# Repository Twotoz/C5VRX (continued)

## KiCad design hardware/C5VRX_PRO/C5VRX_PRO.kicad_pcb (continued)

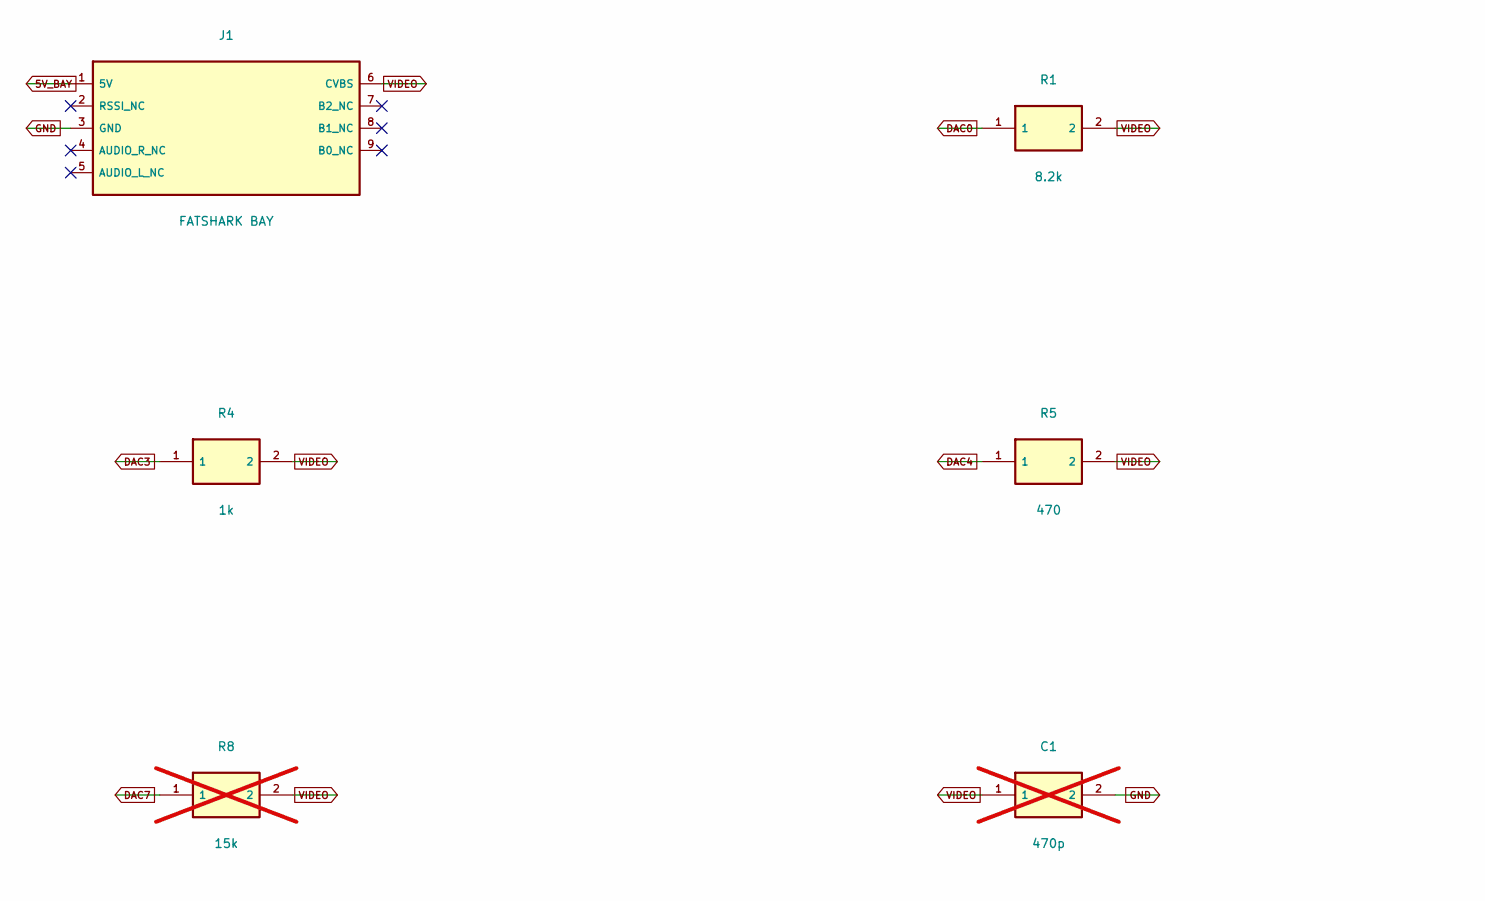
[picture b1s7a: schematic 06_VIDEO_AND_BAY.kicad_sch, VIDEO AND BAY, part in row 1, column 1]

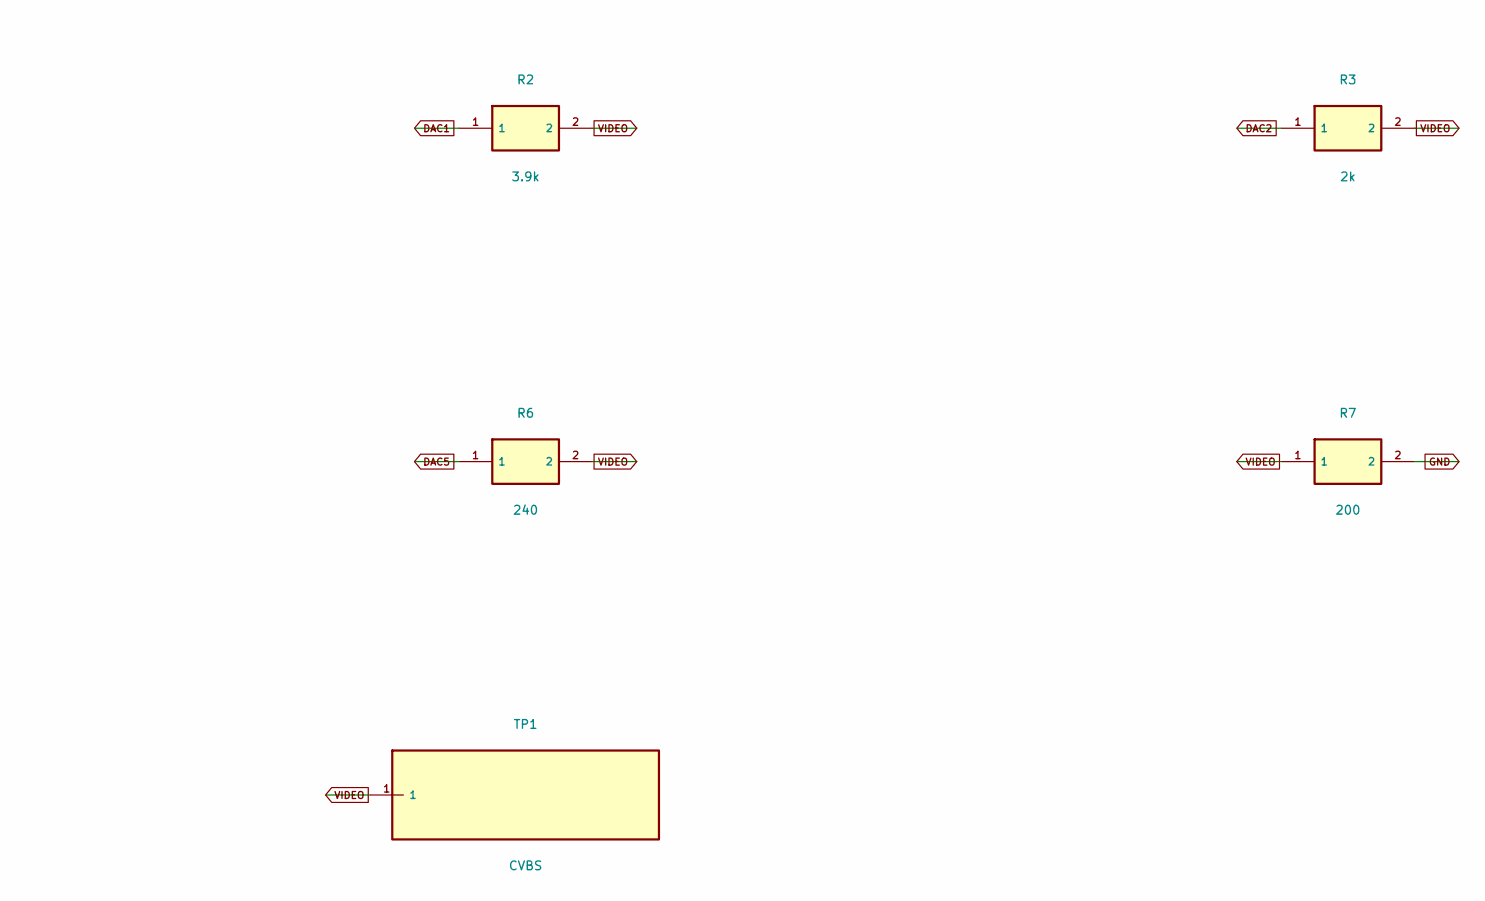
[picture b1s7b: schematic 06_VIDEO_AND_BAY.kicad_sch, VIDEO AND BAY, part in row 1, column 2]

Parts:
C1: 470p; Capacitor_SMD__C_0402_1005Metric; MPN GRM1555C1H471JA01D; not fitted
J1: FATSHARK BAY; FatShark_Header_1x09; MPN CUSTOM_1x09_P2.54_BAY
R1: 8.2k; Resistor_SMD__R_0402_1005Metric; MPN RT0402BRD078K2L
R2: 3.9k; Resistor_SMD__R_0402_1005Metric; MPN RT0402BRD073K9L
R3: 2k; Resistor_SMD__R_0402_1005Metric; MPN RT0402BRD072KL
R4: 1k; Resistor_SMD__R_0402_1005Metric; MPN RT0402BRD071KL
R5: 470; Resistor_SMD__R_0402_1005Metric; MPN RT0402BRD07470RL
R6: 240; Resistor_SMD__R_0402_1005Metric; MPN RT0402BRD07240RL
R7: 200; Resistor_SMD__R_0402_1005Metric; MPN RT0402BRD07200RL
R8: 15k; Resistor_SMD__R_0402_1005Metric; MPN RT0402BRD0715KL; not fitted
TP1: CVBS; TestPoint__TestPoint_Pad_D1.5mm; MPN PCB_FEATURE

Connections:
5V_BAY: J1.1 (5V); also elsewhere on the board
DAC0: R1.1; also elsewhere on the board
DAC1: R2.1; also elsewhere on the board
DAC2: R3.1; also elsewhere on the board
DAC3: R4.1; also elsewhere on the board
DAC4: R5.1; also elsewhere on the board
DAC5: R6.1; also elsewhere on the board
DAC7: R8.1; also elsewhere on the board
GND: C1.2, J1.3 (GND), R7.2; also elsewhere on the board
VIDEO: C1.1, J1.6 (CVBS), R1.2, R2.2, R3.2, R4.2, R5.2, R6.2, R7.1, R8.2, TP1.1

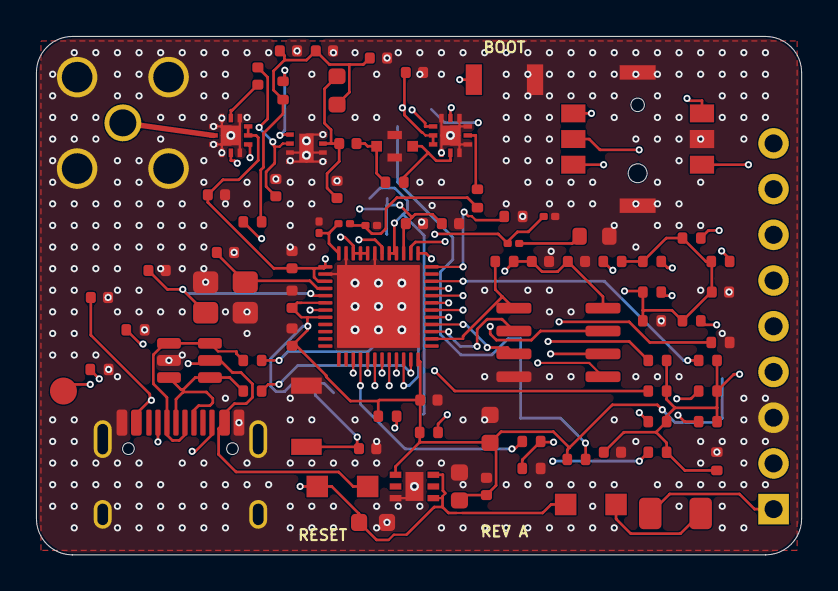
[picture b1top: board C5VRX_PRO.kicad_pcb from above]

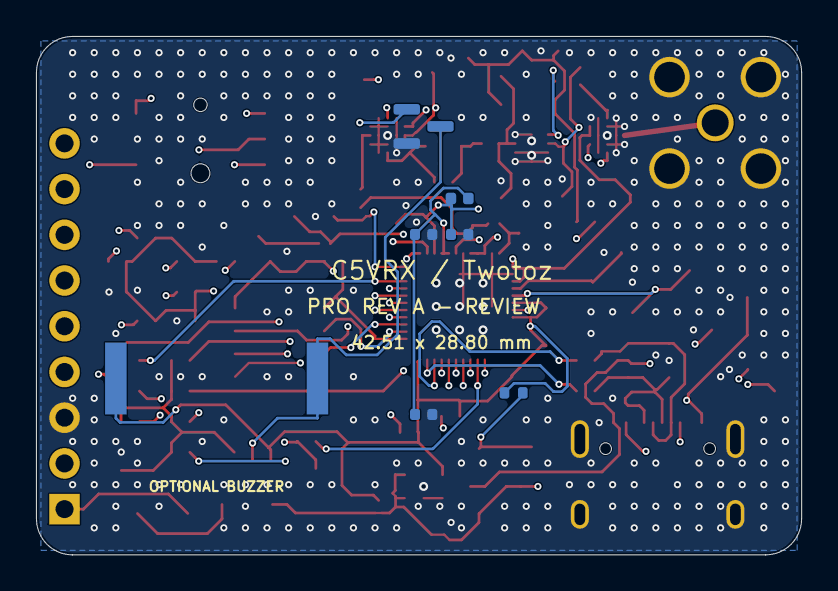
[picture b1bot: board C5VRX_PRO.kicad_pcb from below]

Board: 4 copper layers, 42.5 x 28.8 mm, 91 parts (7 on the bottom side), 57 nets.

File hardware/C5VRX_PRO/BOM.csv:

Reference,Value,Manufacturer,MPN,Footprint,Populate,Note,Datasheet
U1,ESP32-C5HR2,Espressif,ESP32-C5HR2,PRO:Package_DFN_QFN__QFN-48-1EP_6x6mm_P0.4mm_EP4.6x4.6mm,YES,,https://www.espressif.com/sites/default/files/documentation/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
U2,W25Q64JVSSIQ,Winbond,W25Q64JVSSIQ,PRO:Package_SO__SOIC-8_3.9x4.9mm_P1.27mm,YES,,
R10,10k,Yageo,RC0402FR-0710KL,PRO:Resistor_SMD__R_0402_1005Metric,YES,1%; ,
C10,100n,Murata,GRM155R71C104KA88D,PRO:Capacitor_SMD__C_0402_1005Metric,YES,,
C11,1u,Murata,GRM155R61A105KE15D,PRO:Capacitor_SMD__C_0402_1005Metric,YES,,
Y1,48MHz / CL18pF,Abracon,ABM8-48.000MHZ-B2-T,PRO:Crystal__Crystal_SMD_3225-4Pin_3.2x2.5mm,YES,,
C12,27p,Murata,GRM1555C1H270JA01D,PRO:Capacitor_SMD__C_0402_1005Metric,YES,Initial CL value; tune with measured stray capacitance,
C13,27p,Murata,GRM1555C1H270JA01D,PRO:Capacitor_SMD__C_0402_1005Metric,YES,,
R11,10k,Yageo,RC0402FR-0710KL,PRO:Resistor_SMD__R_0402_1005Metric,YES,1%; ,
C14,1u,Murata,GRM155R61A105KE15D,PRO:Capacitor_SMD__C_0402_1005Metric,YES,,
R12,10k,Yageo,RC0402FR-0710KL,PRO:Resistor_SMD__R_0402_1005Metric,YES,1%; ,
R13,10k,Yageo,RC0402FR-0710KL,PRO:Resistor_SMD__R_0402_1005Metric,YES,1%; GPIO27 high for USB download boot; keep loopback loading small,
R14,100k,Yageo,RC0402FR-07100KL,PRO:Resistor_SMD__R_0402_1005Metric,YES,"1%; GPIO7 JTAG strap, no LED loading",
R15,100k,Yageo,RC0402FR-07100KL,PRO:Resistor_SMD__R_0402_1005Metric,YES,1%; Fail to passive bypass during reset,
C20,100n,Murata,GRM155R71C104KA88D,PRO:Capacitor_SMD__C_0402_1005Metric,YES,,
C21,100n,Murata,GRM155R71C104KA88D,PRO:Capacitor_SMD__C_0402_1005Metric,YES,,
C22,100n,Murata,GRM155R71C104KA88D,PRO:Capacitor_SMD__C_0402_1005Metric,YES,,
C23,100n,Murata,GRM155R71C104KA88D,PRO:Capacitor_SMD__C_0402_1005Metric,YES,,
C24,100n,Murata,GRM155R71C104KA88D,PRO:Capacitor_SMD__C_0402_1005Metric,YES,,
C25,100n,Murata,GRM155R71C104KA88D,PRO:Capacitor_SMD__C_0402_1005Metric,YES,,
C26,100n,Murata,GRM155R71C104KA88D,PRO:Capacitor_SMD__C_0402_1005Metric,YES,,
C27,10u,Murata,GRM188R61A106KE69D,PRO:Capacitor_SMD__C_0603_1608Metric,YES,,
L2,2nH,Murata,LQG15HS2N0S02D,PRO:Inductor_SMD__L_0402_1005Metric,YES,ESP RF supply initial tuning value,
C28,1u,Murata,GRM155R61A105KE15D,PRO:Capacitor_SMD__C_0402_1005Metric,YES,,
C29,100n,Murata,GRM155R71C104KA88D,PRO:Capacitor_SMD__C_0402_1005Metric,YES,,
J1,FATSHARK BAY,PCBWay sourcing,CUSTOM_1x09_P2.54_BAY,PRO:FatShark_Header_1x09,YES,,
J3,SMA 50R,Amphenol RF,132134,PRO:Connector_Coaxial__SMA_Amphenol_132134_Vertical,YES,"Vertical SMA female, through-hole, antenna normal to PCB",
J4,USB-C,HRO,TYPE-C-31-M-12,PRO:Connector_USB__USB_C_Receptacle_HRO_TYPE-C-31-M-12,YES,,
R20,5.1k,Yageo,RC0402FR-075K1L,PRO:Resistor_SMD__R_0402_1005Metric,YES,1%; ,
R21,5.1k,Yageo,RC0402FR-075K1L,PRO:Resistor_SMD__R_0402_1005Metric,YES,1%; ,
R22,22,Yageo,RC0402FR-0722RL,PRO:Resistor_SMD__R_0402_1005Metric,YES,1%; ,
R23,22,Yageo,RC0402FR-0722RL,PRO:Resistor_SMD__R_0402_1005Metric,YES,1%; ,
U6,USBLC6-2SC6,STMicroelectronics,USBLC6-2SC6,PRO:Package_TO_SOT_SMD__SOT-23-6,YES,,
F1,750mA PTC,Littelfuse,1206L075/13.2WR,PRO:Fuse__Fuse_1206_3216Metric,YES,,
D1,PMEG2010ER,Nexperia,"PMEG2010ER,115",PRO:Diode_SMD__Nexperia_CFP3_SOD-123W,YES,,
D2,PMEG2010ER,Nexperia,"PMEG2010ER,115",PRO:Diode_SMD__Nexperia_CFP3_SOD-123W,YES,,
U7,TLV75733PDRVR,Texas Instruments,TLV75733PDRVR,PRO:Package_DFN_QFN__DFN-6-1EP_2x2mm_P0.65mm_EP1x1.6mm,YES,,
C30,10u,Murata,GRM188R61A106KE69D,PRO:Capacitor_SMD__C_0603_1608Metric,YES,,
C31,10u,Murata,GRM188R61A106KE69D,PRO:Capacitor_SMD__C_0603_1608Metric,YES,,
C32,100n,Murata,GRM155R71C104KA88D,PRO:Capacitor_SMD__C_0402_1005Metric,YES,,
C33,1u,Murata,GRM155R61A105KE15D,PRO:Capacitor_SMD__C_0402_1005Metric,YES,,
SW1,BOOT,Omron,B3U-1000P,PRO:Button_Switch_SMD__SW_SPST_B3U-1000P,YES,,
SW2,RESET,Omron,B3U-1000P,PRO:Button_Switch_SMD__SW_SPST_B3U-1000P,YES,,
SW3,5-WAY JOYSTICK,ALPS Alpine,SKRHABE010,PRO:SW_SKRHABE010_SMD,YES,,
R30,10k,Yageo,RC0402FR-0710KL,PRO:Resistor_SMD__R_0402_1005Metric,YES,1%; ,
R31,22k,Yageo,RC0402FR-0722KL,PRO:Resistor_SMD__R_0402_1005Metric,YES,1%; ,
R32,1k,Yageo,RC0402FR-071KL,PRO:Resistor_SMD__R_0402_1005Metric,YES,1%; ,
R33,2.2k,Yageo,RC0402FR-072K2L,PRO:Resistor_SMD__R_0402_1005Metric,YES,1%; ,
R34,4.7k,Yageo,RC0402FR-074K7L,PRO:Resistor_SMD__R_0402_1005Metric,YES,1%; ,
R35,10k,Yageo,RC0402FR-0710KL,PRO:Resistor_SMD__R_0402_1005Metric,YES,1%; ,
R36,22,Yageo,RC0402FR-0722RL,PRO:Resistor_SMD__R_0402_1005Metric,YES,1%; ,
C34,100n,Murata,GRM155R71C104KA88D,PRO:Capacitor_SMD__C_0402_1005Metric,YES,,
R1,8.2k,Yageo,RT0402BRD078K2L,PRO:Resistor_SMD__R_0402_1005Metric,YES,0.1% thin film; ,
R2,3.9k,Yageo,RT0402BRD073K9L,PRO:Resistor_SMD__R_0402_1005Metric,YES,0.1% thin film; ,
R3,2k,Yageo,RT0402BRD072KL,PRO:Resistor_SMD__R_0402_1005Metric,YES,0.1% thin film; ,
R4,1k,Yageo,RT0402BRD071KL,PRO:Resistor_SMD__R_0402_1005Metric,YES,0.1% thin film; ,
R5,470,Yageo,RT0402BRD07470RL,PRO:Resistor_SMD__R_0402_1005Metric,YES,0.1% thin film; ,
R6,240,Yageo,RT0402BRD07240RL,PRO:Resistor_SMD__R_0402_1005Metric,YES,0.1% thin film; ,
R7,200,Yageo,RT0402BRD07200RL,PRO:Resistor_SMD__R_0402_1005Metric,YES,0.1% thin film; ,
R8,15k,Yageo,RT0402BRD0715KL,PRO:Resistor_SMD__R_0402_1005Metric,DNP,0.1% thin film; Future new LSB; current firmware is six bit,
C1,470p,Murata,GRM1555C1H471JA01D,PRO:Capacitor_SMD__C_0402_1005Metric,DNP,"Optional, verify video bandwidth before fitting",
BZ1,PASSIVE PIEZO,Murata,PKLCS1212E4001-R1,PRO:Buzzer_Beeper__Buzzer_Murata_PKLCS1212E,DNP,Optional reverse side SMD part; verify bay depth,
Q1,2N7002,Nexperia,"2N7002,215",PRO:Package_TO_SOT_SMD__SOT-23,DNP,,
R37,100,Yageo,RC0402FR-07100RL,PRO:Resistor_SMD__R_0402_1005Metric,DNP,1%; ,
R38,100k,Yageo,RC0402FR-07100KL,PRO:Resistor_SMD__R_0402_1005Metric,DNP,1%; ,
U3,PE42422,pSemi,PE42422A-X,PRO:PE42422_QFN12,YES,,
U5,PE42422,pSemi,PE42422A-X,PRO:PE42422_QFN12,YES,,
U4,QPL9504,Qorvo,QPL9504TR7,PRO:QPL9504_DFN8,YES,,
C40,5.6p,Murata,GJM1555C1H5R6CB01D,PRO:Capacitor_SMD__C_0402_1005Metric,YES,,
C41,0.2p,Murata,GJM1555C1HR20BB01D,PRO:Capacitor_SMD__C_0402_1005Metric,YES,,
C42,2.7p,Murata,GJM1555C1H2R7CB01D,PRO:Capacitor_SMD__C_0402_1005Metric,YES,,
C43,0.5p,Murata,GJM1555C1HR50BB01D,PRO:Capacitor_SMD__C_0402_1005Metric,YES,,
L3,18nH,Coilcraft,0603CS-18NXJRU,PRO:Inductor_SMD__L_0603_1608Metric,YES,,
R40,3.9k,Yageo,RC0402FR-073K9L,PRO:Resistor_SMD__R_0402_1005Metric,YES,1%; ,
R41,0,Yageo,RC0402JR-070RL,PRO:Resistor_SMD__R_0402_1005Metric,YES,1%; ,
C44,1n,Murata,GRM155R71H102KA01D,PRO:Capacitor_SMD__C_0402_1005Metric,YES,,
C45,100n,Murata,GRM155R71C104KA88D,PRO:Capacitor_SMD__C_0402_1005Metric,YES,,
C46,1n,Murata,GRM155R71H102KA01D,PRO:Capacitor_SMD__C_0402_1005Metric,YES,,
C47,100n,Murata,GRM155R71C104KA88D,PRO:Capacitor_SMD__C_0402_1005Metric,YES,,
C48,100n,Murata,GRM155R71C104KA88D,PRO:Capacitor_SMD__C_0402_1005Metric,YES,,
FL1,4.90-5.85GHz BPF,Murata,LFB215G37SG8A180,PRO:LFB215G37,DNP,Optional restricted-band assembly; never fit with R42,
R42,0,Yageo,RC0402JR-070RL,PRO:Resistor_SMD__R_0402_1005Metric,YES,1%; Remove when FL1/R43/R44 are fitted,
C50,1p,Murata,GRM0335C1H1R0CA01D,PRO:Capacitor_SMD__C_0201_0603Metric,YES,Chip-side stub/match requires RF review,
L4,1nH,Murata,LQP03TN1N0B02D,PRO:Inductor_SMD__L_0201_0603Metric,YES,,
C51,0.5p,Murata,GRM0335C1HR50BA01D,PRO:Capacitor_SMD__C_0201_0603Metric,YES,,
R45,0,Yageo,RC0402JR-070RL,PRO:Resistor_SMD__R_0402_1005Metric,YES,1%; ,
C52,2p,Murata,GRM0335C1H2R0CA01D,PRO:Capacitor_SMD__C_0201_0603Metric,YES,,
L5,2.7nH,Murata,LQP03TN2N7B02D,PRO:Inductor_SMD__L_0201_0603Metric,YES,,
R46,49.9,Yageo,RC0603FR-0749R9L,PRO:Resistor_SMD__R_0603_1608Metric,YES,"0.1 W; only incidental 2G calibration, not continuous TX",
TP1,CVBS,PCBWay,PCB_FEATURE,PRO:TestPoint__TestPoint_Pad_D1.5mm,YES,,
R39,1k,Yageo,RC0402FR-071KL,PRO:Resistor_SMD__R_0402_1005Metric,DNP,1%; Piezo discharge path; fit with optional buzzer,

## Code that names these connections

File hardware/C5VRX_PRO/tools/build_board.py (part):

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          29:'VDD_SPI',30:'FLASH_D3',31:'FLASH_CLK',32:'FLASH_D0',33:'DAC0',34:'DAC1',35:'IQ_Q2',36:'RF_ACTIVE',
          37:'IQ_I0',38:'BOOT',39:'3V3',40:'3V3_RF',41:'3V3_RF',42:'ANT_2G',43:'GND',44:'3V3',45:'3V3',46:'3V3',
          47:'GND',48:'ANT_5G',49:'GND'}
soc_pins={1:'VDDA6',2:'GND',3:'VDDA7',4:'XTAL_N',5:'XTAL_P',6:'VDDA8',7:'CHIP_PU',8:'VDDPST1',
          **{i+9:('GPIO'+str(i)) for i in range(15)},24:'VDDPST2',25:'SPICS1_INTERNAL',26:'SPICS0',27:'SPIQ',28:'SPIWP',
          29:'VDD_SPI',30:'SPIHD',31:'SPICLK',32:'SPID',**{i+10:'GPIO'+str(i) for i in range(23,29)},
          39:'VDDPST3',40:'VDDA1',41:'VDDA2',42:'ANT_2G',43:'GND',44:'VDDA3',45:'VDDA4',46:'VDDA5',47:'GND',48:'ANT_5G',49:'EP'}
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res('R11','10k','3V3','EN',115,119.7,block='RESET')
cap('C14','1u','EN','GND',115,121.1,block='RESET',mpn='GRM155R61A105KE15D')
res('R12','10k','3V3','BOOT',121,120,block='RESET')
res('R13','10k','3V3','IQ_I0',121,121.5,block='RESET',note='GPIO27 high for USB download boot; keep loopback loading small')
res('R14','100k','BUZZ_PWM','GND',135,113,block='RESET',note='GPIO7 JTAG strap, no LED loading')
res('R15','100k','RF_ACTIVE','GND',123,109.5,block='RF',note='Fail to passive bypass during reset')

# Local decoupling at every supply group. RF supply pins 40/41 use a series inductor.
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
# RF: two switches provide a passive calibration/strong-signal path.
for ref,common,x,rot in [('U3','ANTENNA',109,180),('U5','RF_SOC',121,0)]:
    add(ref,'PE42422','PRO:PE42422_QFN12',{1:'GND',2:'LNA_IN_AC' if ref=='U3' else 'FILTER_OUT',3:'GND',4:'GND',5:common,
        6:'GND',7:'GND',8:'RF_BYPASS',9:'GND',10:'RF_ACTIVE',11:'3V3',12:'3V3',13:'GND'},x,105.5,rot,
        mpn='PE42422A-X',maker='pSemi',block='RF',pins={2:'RF2_LNA',5:'RFC',8:'RF1_BYPASS',10:'V1',11:'LS',12:'VDD',13:'EP'})
add('U4','QPL9504','PRO:QPL9504_DFN8',{1:'LNA_BIAS',2:'LNA_IN',3:'GND',4:'GND',5:'GND',6:'GND',7:'LNA_DRAIN',8:'GND',9:'GND'},
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add('R46','49.9','Resistor_SMD:R_0603_1608Metric',{1:'RF_2G_TERM',2:'GND'},128,109,
    mpn='RC0603FR-0749R9L',maker='Yageo',block='MATCH',note='0.1 W; only incidental 2G calibration, not continuous TX')

# USB-C replaces the large DIY AV jack; bay pin 6 remains the video interface.
parts=[c for c in parts if c['ref'] not in ('J2','R43','R44')]
add('TP1','CVBS','TestPoint:TestPoint_Pad_D1.5mm',{1:'VIDEO'},103,121,mpn='PCB_FEATURE',maker='PCBWay',block='VIDEO')
locations={
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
